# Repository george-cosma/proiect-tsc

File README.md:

# Openbook - Proiect TSC - by Cosma George

## Block Diagram

## Overview ESP32

1. **GND (All 11 pins)** - Connected to the ground plane
2. **3V3 (Pin 2)** - Connected to the 3.3V power rail
3. **EN (Pin 3)** - Enable pin - activates the ESP32-C6 when power is applied.
4. **IO0 (Pin 8)** - INT_RTC (RTC Interrupt) connects to the RTC module to receive time-based interrupts
5. **IO1 (Pin 9)** - 32KHz clock signal received from Oscilator
6. **IO2 (Pin 27)** - MISO (SPI Master In Slave Out). Connects to External Storage, External I/O and E-Paper Display Header
7. **IO3 (Pin 26)** - EPD_BUSY connects to the E-Paper display's busy signal to monitor when the display is busy
8. **IO4 (Pin 4)** - SS_SD (SD Card Chip Select)
9. **IO5 (Pin 5)** - EPD_DC (E-Paper Display Data/Command) to command the E-Paper Display via the Header
10. **IO6 (Pin 6)** - SCK (SPI Clock) to provide a clock frame of reference to communicate via SPI
11. **IO7 (Pin 7)** - MOSI (SPI Master Out Slave In) Connects to External Storage, External I/O and E-Paper Display Header
12. **IO8 (Pin 10)** - GPIO8 general purpose I/O, connected to a test pad (?)
13. **IO9 (Pin 15)** - IO/BOOT connected to an external push button with pull-up resistors.
14. **I10 (Pin 11)** - EPD_CS (E-Paper Display Chip Select) connects directly to the E-Paper Display Header to select when comunicating/receiving data from it.
15. **IO11 (Pin 11)** - FLASH_CS (SPI Flash Chip Select) connects to the NOR Flash memory to select when communicating/receiving data from it.
16. **IO12 (Pin 12)** - USB_D- (USB Data-) connects directly to the USB-C connector and is used for USB communication via UART.
17. **IO13 (Pin 13)** - USB_D+ (USB Data+) connects directly to the USB-C connector and is used for USB communication via UART.
18. **IO15 (Pin 14)** - IO/CHANGE connected to a push button with pull-up resistors, for user input
19. **TXD0/GPIO16 (Pin 25)** - TX (UART Transmit) connected to test pads - for debugging or programming
20. **RXD0/GPIO17 (Pin 24)** - RX (UART Receive) connected to test pads - for debugging or programming
21. **IO18 (Pin 16)** - RTC_RST (RTC Reset) connects to the reset pin of the real-time clock module
22. **IO19 (Pin 17)** - I2C_PW (I2C Power control) controls power to the I2C peripherals
23. **IO20 (Pin 18)** - EPD_3V3_C (E-Paper Display 3.3V control) controls power to the E-Paper display via a transistor. Used to turn on/off the display to save power when not in use.
24. **IO21 (Pin 19)** - SDA (I2C Data) connects to the I2C peripherals for data communication
25. **IO22 (Pin 20)** - SCL (I2C Clock) connects to the I2C peripherals for clock signal
26. **IO23 (Pin 21)** - EPD_RST (E-Paper Display Reset) connects to the E-Paper display's reset pin to reset the display when needed

## Components overview

1. **ESP32-C6-WROOM-1-N8**
   - Purpose: Main microcontroller/SoC
   - Interfaces: Everything
2. **W25Q512JVEIQ**
   - Purpose: External NOR flash memory
   - Interface: SPI
3. **MAX17048G+T10**
   - Purpose: IC to monitor Li-Po battery level
   - Interface: I2C
4. **XC6220A331MR-G**
   - Purpose: LDO voltage regulator
   - Interface: None (power supply)
5. **USBLC6-2SC6Y**
   - Purpose: USB ESD protection IC
   - Interface: USB D+/D- UART lines
6. **MCP73831**
   - Purpose: Single-cell Li-Po battery charging controller
   - Interface: None (power supply)
7. **BME688**
   - Purpose: Environmental sensor
   - Interface: I2C
8. **BD5229G-TR + Buttons**
   - Purpose: Voltage supervisor + Buttons
   - Interface: GPIO
9. **DS3231SN**
   - Purpose: Real-time clock with crystal oscillator
   - Interface: I2C and GPIO
10. **112A-TAAR-R03_ATTEND**
    - Purpose: SD card slot for storage
    - Interface: SPI
11. **FH34SRJ-24S-0.5SH_99_**
    - Purpose: E-Paper Display Headder
    - Interface: SPI + GPIO
12. **SAMACSYS_PARTS_USB4110-GF-A**
    - Purpose: USB-C connector
    - Interface: USB D+/D- UART

## Bill of Materials

| Qty | Device                       | Value                                    | Parts                                                                                                       | Description                                                                                                                   | BUY                                                                                                                                | DATASHEET                                                                                                                             |
|-----|------------------------------|------------------------------------------|-------------------------------------------------------------------------------------------------------------|-------------------------------------------------------------------------------------------------------------------------------|------------------------------------------------------------------------------------------------------------------------------------|---------------------------------------------------------------------------------------------------------------------------------------|
| 1   | 112A-TAAR-R03_ATTEND         | -                                        | J4                                                                                                          | Micro SD Card Socket, Push-Push Type, Top Mount,   SMT, H=1.83mm, 10u                                                         | [Buy here](https://www.tme.eu/ro/details/mcc-sdmicro/conectori-pentru-cartele/attend/112a-taar-r03/)                                           | [Datasheet here](https://cdn.soselectronic.com/productdata/bd/ac/42954337/112a-taar-r03.pdf)                                                            |
| 1   | 744043680IND_4828-WE-TPC_WRE | 68uH                                     | L1                                                                                                          |                                                                                                                               | [Buy here](https://ro.mouser.com/ProductDetail/Wurth-Elektronik/744043008?qs=PGXP4M47uW6hG5GeMvqOSQ%3D%3D)                                     | [Datasheet here](https://www.we-online.com/components/products/datasheet/744043008.pdf)                                                                 |
| 1   | ADAFRUIT_LEDCHIP-LED0603     | -                                        | CHG_LED                                                                                                     | LED                                                                                                                           | [Buy here](https://ro.mouser.com/ProductDetail/ROHM-Semiconductor/CSL1104WBBW1?qs=DRkmTr78QAQ%252BqzFWy9Kqog%3D%3D)                            | [Datasheet here](https://fscdn.rohm.com/en/products/databook/datasheet/opto/led/chip_mono/csl1104wbbw1-e.pdf)                                           |
| 2   | AVX SD0805S020S1R0           | -                                        | D2, D7                                                                                                      | Schottky Barrier Rectifier   Diode                                                                                            | [Buy here](https://ro.mouser.com/ProductDetail/KYOCERA-AVX/SD0805S020S1R0?qs=jCA%252BPfw4LHbpkAoSnwrdjw%3D%3D)                                 | [Datasheet here](https://ro.mouser.com/datasheet/2/40/schottky-3165252.pdf)                                                                             |
| 1   | BD5229G-TR                   | -                                        | IC1                                                                                                         | Voltage Detector with Adjustable Delay Time                                                                                   | [Buy here](https://ro.mouser.com/ProductDetail/ROHM-Semiconductor/BD5229G-TR?qs=4kLU8WoGk0vvnhrrYwdszw%3D%3D)                                  | [Datasheet here](https://fscdn.rohm.com/en/products/databook/datasheet/ic/power/voltage_detector/bd52xxg-e.pdf)                                         |
| 1   | BME688                       | -                                        | SENSOR2                                                                                                     | Integrated Environmental   Unit                                                                                               | [Buy here](https://ro.mouser.com/ProductDetail/Bosch-Sensortec/BME688?qs=IS%252B4QmGtzzqQoVDscqwx3A%3D%3D)                                     | [Datasheet here](https://ro.mouser.com/datasheet/2/783/bst_bme688_fl000-2307034.pdf)                                                                    |
| 1   | Button                       | BOOT_BUTTON, CHANGE_BUTTON_ RESET_BUTTON | U$1, U$2, U$3                                                                                               |                                                                                                                               | [Buy here](https://ro.mouser.com/ProductDetail/Panasonic/EVQ-9P701P?qs=NPkb10g2yLBKCwpELvsGNg%3D%3D)                                           | [Datasheet here](https://4donline.ihs.com/images/VipMasterIC/IC/PANA/PANAS45028/PANAS45028-1.pdf?hkey=CECEF36DEECDED6468708AAF2E19C0C6)                 |
| 1   | Capacitor                    | 0.1uF/50V                                | EPD_C5                                                                                                      | CAPACITOR, European symbol                                                                                                    | [Buy here](https://ro.mouser.com/ProductDetail/WIMA/SMDIC03100KA00MP00?qs=sGAEpiMZZMukHu%252BjC5l7YTpCIjlvjqqOhx6cMTURzRs%3D)                  | [Datasheet here](https://ro.mouser.com/datasheet/2/440/e_WIMA_SMD_PPS-1139945.pdf)                                                                      |
| 8   | Capacitor                    | 100nF                                    | C1, C2, C4_USB, C6, C8, C9, C10, C_DELAY                                                                    | CAPACITOR, European symbol                                                                                                    | [Buy here](https://ro.mouser.com/ProductDetail/Vishay-Vitramon/VJ1210Y104KBBAT4X?qs=sGAEpiMZZMukHu%252BjC5l7YUsqw7r0AP18aXzCLTFnl8Y%3D)        | [Datasheet here](https://www.vishay.com/doc?45198)                                                                                                      |
| 1   | Capacitor                    | 10uF                                     | C7                                                                                                          | CAPACITOR, European symbol                                                                                                    | [Buy here](https://ro.mouser.com/ProductDetail/KYOCERA-AVX/KGM03DS60E106MH?qs=sGAEpiMZZMukHu%252BjC5l7YWACoop%252BoD4TOu1wAFQEK4E%3D)          | [Datasheet here](https://ro.mouser.com/datasheet/2/40/cx5r_KGM-3223198.pdf)                                                                             |
| 1   | Capacitor                    | 1uF                                      | C5                                                                                                          | CAPACITOR, European symbol                                                                                                    | [Buy here](https://ro.mouser.com/ProductDetail/WIMA/SMDTC04100VA00KR00?qs=sGAEpiMZZMukHu%252BjC5l7YeyzaTQ4jBxXydaOoMKRkJQ%3D)                  | [Datasheet here](https://ro.mouser.com/datasheet/2/440/e_WIMA_SMD_PET-1139826.pdf)                                                                      |
| 9   | Capacitor                    | 1uF/50V                                  | EPD_C1, EPD_C2, EPD_C6,   EPD_C7, EPD_C8, EPD_C9, EPD_C10, EPD_C11, EPD_C12                                 | CAPACITOR, European symbol                                                                                                    | [Buy here](https://ro.mouser.com/ProductDetail/WIMA/SMDTC04100VA00KR00?qs=sGAEpiMZZMukHu%252BjC5l7YeyzaTQ4jBxXydaOoMKRkJQ%3D)                  | [Datasheet here](https://ro.mouser.com/datasheet/2/440/e_WIMA_SMD_PET-1139826.pdf)                                                                      |
| 5   | Capacitor                    | 4.7uF                                    | C1_BAT, C1_BAT1, C1_BAT2, C2_BAT, C5_USB                                                                    | CAPACITOR, European symbol                                                                                                    | [Buy here](https://ro.mouser.com/ProductDetail/WIMA/SMDTD04470YA00KS00?qs=sGAEpiMZZMukHu%252BjC5l7YTpCIjlvjqqOpdXtMIjonJE%3D)                  | [Datasheet here](https://ro.mouser.com/datasheet/2/440/e_WIMA_SMD_PET-1139826.pdf)                                                                      |
| 1   | Capacitor                    | 4.7uF/25V                                | C4                                                                                                          | CAPACITOR, European symbol                                                                                                    | [Buy here](https://ro.mouser.com/ProductDetail/WIMA/SMDTD04470YA00KS00?qs=sGAEpiMZZMukHu%252BjC5l7YTpCIjlvjqqOpdXtMIjonJE%3D)                  | [Datasheet here](https://ro.mouser.com/datasheet/2/440/e_WIMA_SMD_PET-1139826.pdf)                                                                      |
| 1   | CPH3225A                     | -                                        | C10_SUPERCAP                                                                                                | Cap 0.011F 3.3V 1210 Flat Check availability                                                                                  | [Buy here](https://ro.mouser.com/ProductDetail/Seiko-Semiconductors/CPH3225A?qs=3etwrb1wR%252BhUOph6lAO7eg%3D%3D)                              | [Datasheet here](https://ro.mouser.com/datasheet/2/360/Seiko_Instruments_MicroBattery_E_20230330_2024Jan_-3561061.pdf)                                  |
| 2   | DMG2305UX-7                  | 20V/4.2A/52mO/1.4W                       | Q1, Q2                                                                                                      | P-channel MOSFETs                                                                                                             | [Buy here](https://ro.mouser.com/ProductDetail/Diodes-Incorporated/DMG2305UX-7?qs=L1DZKBg7t5F%2FNBHrjfxC%252Bg%3D%3D)                          | [Datasheet here](https://www.diodes.com/assets/Datasheets/DMG2305UX.pdf)                                                                                |
| 1   | DS3231SN#                    | -                                        | U3                                                                                                          | Real Time Clock Serial 16-Pin SOIC W T/R     Check availability                                                               | [Buy here](https://ro.mouser.com/ProductDetail/Analog-Devices-Maxim-Integrated/DS3231SN?qs=1eQvB6Dk1vhUlr8%2FOrV0Fw%3D%3D)                     | [Datasheet here](https://ro.mouser.com/datasheet/2/609/DS3231-3421123.pdf)                                                                              |
| 1   | ESP32-C6-WROOM-1-N8          | -                                        | U2                                                                                                          |                                                                                                                               | [Buy here](https://ro.mouser.com/ProductDetail/Espressif-Systems/ESP32-C6-WROOM-1-N8?qs=8Wlm6%252BaMh8ST02Gmwp74cw%3D%3D)                      | [Datasheet here](https://ro.mouser.com/datasheet/2/891/Espressif_ESP32_C6_WROOM_1__Datasheet_V0_1_PRELIMI-3239987.pdf)                                  |
| 1   | FH34SRJ-24S-0.5SH_99_        | -                                        | J1                                                                                                          |  (0.50mm)   Surface Mount, Right Angle                                                                                        | [Buy here](https://ro.mouser.com/ProductDetail/Hirose-Connector/FH34SRJ-24S-0.5SH99?qs=vcbW%252B4%252BSTIpKBl5ap9J8Fw%3D%3D)                   | [Datasheet here](https://ro.mouser.com/datasheet/2/185/FH34SRJ_24S_0_5SH_99__CL0580_1255_6_99_2DDrawing_0-1615044.pdf)                                  |
| 1   | MAX17048G+T10                | -                                        | U4                                                                                                          |                                                                                                                               | [Buy here](https://ro.mouser.com/ProductDetail/Analog-Devices-Maxim-Integrated/MAX17048G%2bT10?qs=D7PJwyCwLAoGnnn8jEPRBQ%3D%3D)                | [Datasheet here](https://ro.mouser.com/datasheet/2/609/MAX17048_MAX17049-3469099.pdf)                                                                   |
| 3   | MBR0530                      | -                                        | D3, D4, D5                                                                                                  | ON SEMICONDUCTOR - MBR0530 - DIODE, SCHOTTKY, 0.5A,   30V, SOD-123                                                            | [Buy here](https://ro.mouser.com/ProductDetail/onsemi/MBR0530T3G?qs=3JMERSakebpEmdUS6GetdQ%3D%3D)                                              | [Datasheet here](https://www.onsemi.com/PowerSolutions/product.do?id=MBR0530T3G)                                                                        |
| 1   | MCP73831                     | -                                        | U10                                                                                                         | MCP73831T Li-Ion, Li-Pol   Controller                                                                                         | [Buy here](https://ro.mouser.com/ProductDetail/Microchip-Technology/MCP73831T-2ACI-OT?qs=yUQqVecv4qvbBQBGbHx0Mw%3D%3D)                         | [Datasheet here](https://ro.mouser.com/datasheet/2/268/MCP73831_Family_Data_Sheet_DS20001984H-3441711.pdf)                                              |
| 6   | PGB1010603MR                 | -                                        | D6, D8, D9, D10, D11, D12                                                                                   |                                                                                                                               | [Buy here](https://ro.mouser.com/ProductDetail/Littelfuse/PGB1010603MR?qs=gu7KAQ731URLg4GSnNNN7Q%3D%3D)                                        | [Datasheet here](https://www.littelfuse.com/assetdocs/pulseguard-esd-suppressors-pgb1-datasheet?assetguid=8a337998-d54d-466b-be4e-dc5bcd1f9321)         |
| 1   | QWIIC_CONNECTORJS-1MM        | -                                        | J3                                                                                                          | SparkFun I2C Standard   Qwiic Connector                                                                                       | [Buy here](https://www.sparkfun.com/qwiic-jst-connector-smd-4-pin-horizontal.html)                                                             | [Datasheet here](https://cdn.sparkfun.com/assets/parts/1/2/2/8/9/Qwiic_Connector_Datasheet.pdf)                                                         |
| 1   | RCL_CPOL-EUCT3528            | 100uF TANT                               | C3                                                                                                          | POLARIZED CAPACITOR, European symbol                                                                                          | [Buy here](https://ro.mouser.com/ProductDetail/Vishay-Sprague/593D107X9020E2TE3?qs=sGAEpiMZZMsh%252B1woXyUXj7FzGMN%252BX%252BZrA47dYxLY0LY%3D) | [Datasheet here](https://www.vishay.com/doc?40005)                                                                                                      |
| 1   | Resistance                   | 0.47                                     | R3                                                                                                          | RESISTOR, European symbol                                                                                                     | [Buy here](https://ro.mouser.com/ProductDetail/Panasonic/ERJ-14BQFR47U?qs=sGAEpiMZZMukHu%252BjC5l7Ye4WQ9FrfA3YXh5QopT%252BLe8%3D)              | [Datasheet here](https://industrial.panasonic.com/cdbs/www-data/pdf/RDN0000/AOA0000C313.pdf)                                                            |
| 1   | Resistance                   | 100K                                     | R1_PWRBUS                                                                                                   | RESISTOR, European symbol                                                                                                     | [Buy here](https://ro.mouser.com/ProductDetail/Vishay-Thin-Film/PTN0603E1003BBT1?qs=sGAEpiMZZMukHu%252BjC5l7YTJuwIl8JpxyJ2Y%2FdokIqGc%3D)      | [Datasheet here](https://www.vishay.com/doc?60026)                                                                                                      |
| 16  | Resistance                   | 10K                                      | R1, R1_PINH, R1_PINH1,   R2_PINH, R2_PINH1, R4, R5, R6, R7, R8, R9, R10, R_BOOT, R_CHANGE, R_CL1,   R_RESET | RESISTOR, European symbol                                                                                                     | [Buy here](https://ro.mouser.com/ProductDetail/Vishay-Draloric/RCA040210K0JNED?qs=sGAEpiMZZMukHu%252BjC5l7YQO3gf4mVmUu96cUBYHYfeM%3D)          | [Datasheet here](https://www.vishay.com/doc?20037)                                                                                                      |
| 1   | Resistance                   | 15                                       | R_CAPACITOR                                                                                                 | RESISTOR, European symbol                                                                                                     | [Buy here](https://ro.mouser.com/ProductDetail/ROHM-Semiconductor/KTR03EZPJ150?qs=sGAEpiMZZMtlubZbdhIBICz%2FtfrlArmddJ1cOrAnKnc%3D)            | [Datasheet here](https://www.rohm.com/datasheet?p=KTR03EZPJ&dist=Mouser&media=referral&source=mouser.com&campaign=Mouser)                               |
| 1   | Resistance                   | 2.2                                      | R2                                                                                                          | RESISTOR, European symbol                                                                                                     | [Buy here](https://ro.mouser.com/ProductDetail/ROHM-Semiconductor/KTR18EZPJ2R2?qs=sGAEpiMZZMtlubZbdhIBICz%2FtfrlArmdtqB%2FNN1ZHWQ%3D)          | [Datasheet here](https://www.rohm.com/datasheet?p=KTR18EZPJ&dist=Mouser&media=referral&source=mouser.com&campaign=Mouser)                               |
| 1   | Resistance                   | 200                                      | R1_BAT                                                                                                      | RESISTOR, European symbol                                                                                                     | [Buy here](https://ro.mouser.com/ProductDetail/ROHM-Semiconductor/KTR10EZPJ201?qs=sGAEpiMZZMtlubZbdhIBIGrVcSH3vih40FduZYz%252BzpI%3D)          | [Datasheet here](https://www.rohm.com/datasheet?p=KTR10EZPJ&dist=Mouser&media=referral&source=mouser.com&campaign=Mouser)                               |
| 1   | Resistance                   | 2K                                       | R2_BAT                                                                                                      | RESISTOR, European symbol                                                                                                     | [Buy here](https://ro.mouser.com/ProductDetail/Vishay-Sfernice/P0805Y2001BBW?qs=sGAEpiMZZMtlubZbdhIBIL5MhBxehHgV0bOCcoqDPYA%3D)                | [Datasheet here](https://4donline.ihs.com/images/VipMasterIC/IC/VISH/VISH-S-A0007087424/VISH-S-A0007087424-1.pdf?hkey=CECEF36DEECDED6468708AAF2E19C0C6) |
| 2   | Resistance                   | 5K1                                      | R2-USB, R2-USB1                                                                                             | RESISTOR, European symbol                                                                                                     | [Buy here](https://ro.mouser.com/ProductDetail/Vishay-Dale/TNPW04025K10BYEP?qs=sGAEpiMZZMtlubZbdhIBIJ2VesJ5mRFWaQfYu47si8Y%3D)                 | [Datasheet here](https://www.vishay.com/doc?28758)                                                                                                      |
| 1   | SAMACSYS_PARTS_USB4110-GF-A  | -                                        | J2                                                                                                          | CONN USB 2.0 TYPE-C R/A   SMT                                                                                                 | [Buy here](https://ro.mouser.com/ProductDetail/GCT/USB4110-GF-A?qs=KUoIvG%2F9IlYiZvIXQjyJeA%3D%3D)                                             | [Datasheet here](https://ro.mouser.com/datasheet/2/837/GCT_USB4110_Product_Drawing___20k_cycles-3455479.pdf)                                            |
| 1   | SI1308EDL-T1-GE3             | -                                        | Q3                                                                                                          | MOSFET N-Ch 30V 1.5A TrenchFET SC70 Vishay   Si1308EDL-T1-GE3 N-channel MOSFET Transistor, 1.5 A, 30 V, 3-Pin SC-70           | [Buy here](https://ro.mouser.com/ProductDetail/Vishay-Semiconductors/SI1308EDL-T1-GE3?qs=bX1%252BNvsK%2FBramh9tgpOaEw%3D%3D)                   | [Datasheet here](https://www.vishay.com/doc?63399)                                                                                                      |
| 1   | USBLC6-2SC6Y                 | -                                        | D1                                                                                                          | Low Cap. ESD Protection   Auto SOT-23-6 STMicroelectronics USBLC6-2SC6Y, Dual Uni-Directional TVS Diode   Array, 6-Pin SOT-23 | [Buy here](https://ro.mouser.com/ProductDetail/STMicroelectronics/USBLC6-2SC6Y?qs=gNDSiZmRJS%2FOgDexvXkdow%3D%3D)                              | [Datasheet here](https://ro.mouser.com/datasheet/2/389/usblc6_2sc6y-1852505.pdf)                                                                        |
| 1   | VARISTOR CN1812              | -                                        | PFMF.050.1                                                                                                  | VARISTOR                                                                                                                      | [Buy here](https://ro.mouser.com/ProductDetail/Schurter/PFMF.050.2?qs=1auRipcfynCums5v1iucSA%3D%3D)                                            | [Datasheet here](https://ro.mouser.com/datasheet/2/358/typ_PFMF-1275918.pdf)                                                                            |
| 1   | W25Q512JVEIQ                 | -                                        | U1                                                                                                          |                                                                                                                               | [Buy here](https://ro.mouser.com/ProductDetail/Winbond/W25Q512JVEIQ?qs=l7cgNqFNU1jw6svr3at6tA%3D%3D)                                           | [Datasheet here](https://ro.mouser.com/datasheet/2/949/Winbond_W25Q512JV_Datasheet-3240039.pdf)                                                         |
| 1   | XC6220A331MR-G               | -                                        | IC4                                                                                                         | LDO Voltage Regulators                                                                                                        | [Buy here](https://ro.mouser.com/ProductDetail/Torex-Semiconductor/XC6220A331MR-G?qs=AsjdqWjXhJ8ZSWznL1J0gg%3D%3D)                             | [Datasheet here](https://ro.mouser.com/datasheet/2/760/xc6220-3371556.pdf)                                                                              |
| 1   | Battery                      | -                                        | -                                                                                                           | CELLEVIA BATTERIES LP584174, 3.7V 1800 mAh | [Buy here](https://www.tme.eu/ro/details/accu-lp584174_cl/acumulatori/cellevia-batteries/l584174/) | [Datasheet here](https://www.tme.eu/Document/e0683d8c34e6d878124489f71bffb6ee/cel0014.pdf) |
| 1   | E-Paper Display              | -                                        | -                                                                                                           | 7.5''  800x480 px 125 DPI | [Buy here](https://www.waveshare.com/7.5inch-e-paper-hat.htm) | [Datasheet here](https://files.waveshare.com/upload/6/60/7.5inch_e-Paper_V2_Specification.pdf) |

## Implementation Notes/Details

- I've attempted to replicate the schematic as closely as possible, but there might be minor differences in terms of label size, label and text positioning,
compactness of components.
- The PCB was routed 100% manually, with no auto-router used. Both a top and bottom ground plane were used, as per the design requirements, and extensive via stitching was used to ensure a low-impedance ground connection. Via stiching can be removed if design parameters change, as additional vias for ground connectivity have been added to the design outside of the stiching process.
- Two visas were used for I2C_PW line, as it was unavoidable to route without crossing another power line. All power lines were routed using 0.3mm without vias and kept as short as possible, and all signal lines were routed using 0.2mm using vias.  
- PCB Thickness was modified to 1mm to ensure it, alongside the display, were able to fit within the given enclosure.
- PCB holes were added for the battery, ESP antenna, and the display header to allow for the ribbon cable to be inserted.
- Silkscreen was made with minimality in mind. Additional marks (lines, extra text) were added when needed to ensure readability.
- Accepted clearence error for USB-C connector.

## Other Images

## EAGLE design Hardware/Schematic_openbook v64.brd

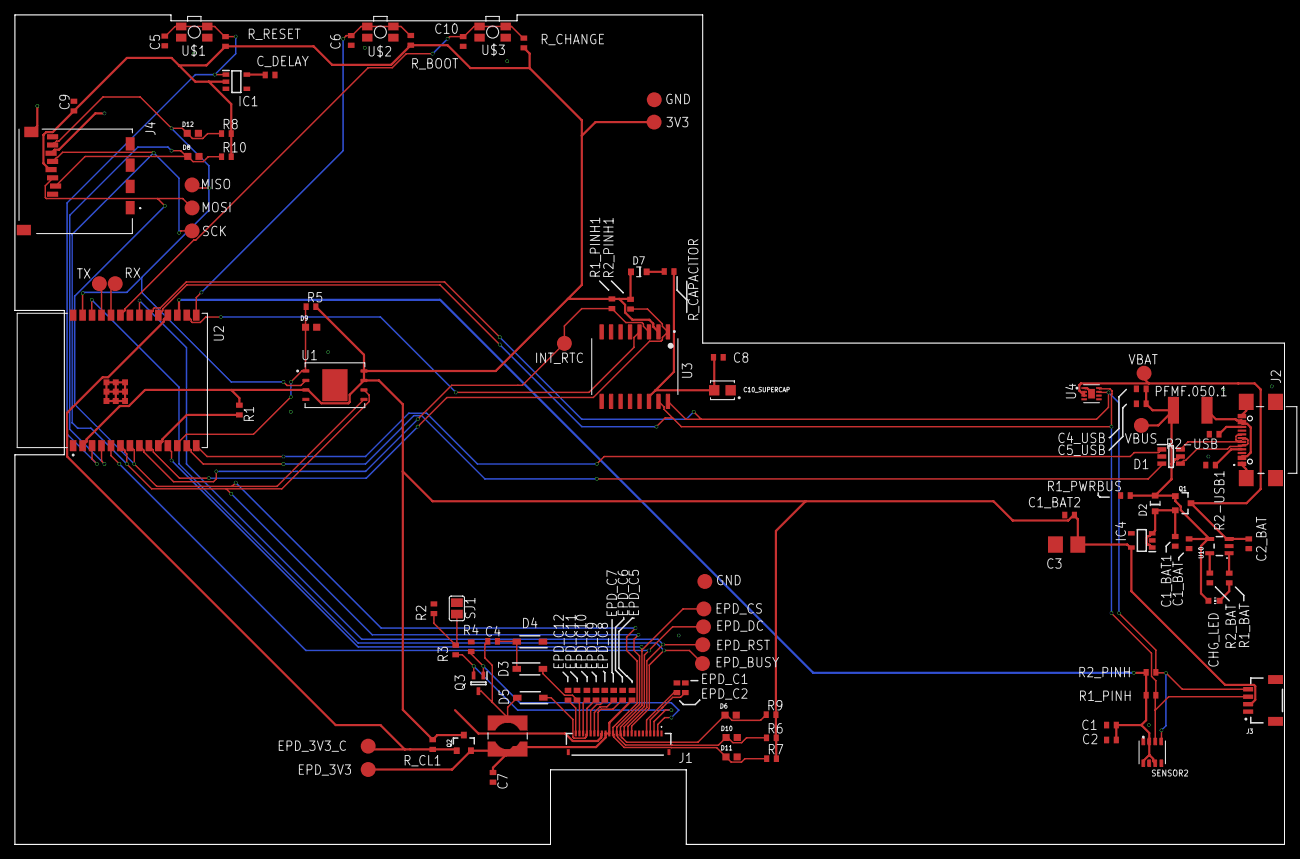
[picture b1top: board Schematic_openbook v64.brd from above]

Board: 2 copper layers, 170.2 x 111.2 mm, 103 parts (0 on the bottom side), 55 nets.

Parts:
C1, C2, C4_USB, C6, C8, C9, C10: 100nF; EAGLE-LTSPICE_C0402
C1_BAT, C1_BAT1, C1_BAT2, C2_BAT, C5_USB: 4.7uF; EAGLE-LTSPICE_C0402
C3: 100uF TANT; RCL_CT3528
C4: 4.7uF/25V; EAGLE-LTSPICE_C0402
C5: 1uF; EAGLE-LTSPICE_C0402
C7: 10uF; EAGLE-LTSPICE_C0402
C10_SUPERCAP: CPH3225A; CAPCP3225X100N
CHG_LED: NA; ADAFRUIT_CHIP-LED0603
C_DELAY: 100nF; EAGLE-LTSPICE_C0402
D1: USBLC6-2SC6Y; SOT95P280X145-6N
D2: ESP32_WROVER_AVX---SD0805S020S1R0_AVX_SD0805S020S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; ESP32_WROVER_AVX---SD0805S020S1R0_AVX_SD0805S020S1R0_0
D3, D4, D5: MBR0530; SOD3716X135N
D6, D8, D9, D10, D11, D12: PGB1010603MR; DIOC1608X36N
D7: SD0805S020S1R0; ESP32_WROVER_AVX---SD0805S020S1R0_AVX_SD0805S020S1R0_0
EPD_C1, EPD_C2, EPD_C6, EPD_C7, EPD_C8, EPD_C9, EPD_C10, EPD_C11, EPD_C12: 1uF/50V; EAGLE-LTSPICE_C0402
EPD_C5: 0.1uF/50V; EAGLE-LTSPICE_C0402
IC1: BD5229G-TR; SOT95P280X125-5N
IC4: XC6220A331MR-G; SOT95P280X120-5N
J1: FH34SRJ-24S-0.5SH_99_; FH34SRJ24S05SH99
J2: SAMACSYS_PARTS_USB4110-GF-A; SAMACSYS_PARTS_USB4110GFA
J3: QWIIC_RIGHT_ANGLE; JST04_1MM_RA
J4: 112A-TAAR-R03_ATTEND; 112ATAARR03ATTEND
L1: 68uH; IND_4828-WE-TPC_WRE
PFMF.050.1: ESP32C6_VARISTORCN1812; ESP32C6_VARISTOR_CT/CN1812
Q1, Q2: 20V/4.2A/52mΩ/1.4W; ESP32_WROVER_SPARKFUN-DISCRETESEMI_SOT23-3
Q3: SI1308EDL-T1-GE3; SOT65P210X110-3N
R1, R1_PINH, R1_PINH1, R2_PINH, R2_PINH1, R5, R6, R7, R8, R9, R10: 10K; ESP32_WROVER_EAGLE-LTSPICE_R0402
R1_BAT: 200; ESP32_WROVER_EAGLE-LTSPICE_R0402
R1_PWRBUS: 100K; ESP32_WROVER_EAGLE-LTSPICE_R0402
R2: 2.2; ESP32_WROVER_EAGLE-LTSPICE_R0402
R2-USB, R2-USB1: 5K1; ESP32_WROVER_EAGLE-LTSPICE_R0402
R2_BAT: 2K; ESP32_WROVER_EAGLE-LTSPICE_R0402
R3: 0.47; ESP32_WROVER_EAGLE-LTSPICE_R0402
R4: 10k; ESP32_WROVER_EAGLE-LTSPICE_R0402
R_BOOT: 10K; ESP32_WROVER_EAGLE-LTSPICE_R0402
R_CAPACITOR: 15; ESP32_WROVER_EAGLE-LTSPICE_R0402
R_CHANGE: 10K; ESP32_WROVER_EAGLE-LTSPICE_R0402
R_CL1: 10K; ESP32_WROVER_EAGLE-LTSPICE_R0402
R_RESET: 10K; ESP32_WROVER_EAGLE-LTSPICE_R0402
SENSOR2: BME688; ESP32_WROVER_BME680_PSON80P300X300X100-8N
SJ1: NA; SJ
TP1, TP2, TP3, TP4, TP5, TP6, TP7, TP8, TP9, TP10, TP11, TP12, TP13, TP14, TP15, TP16, TP17: TPTP20R; TP20R
U1: W25Q512JVEIQ; SON127P600X800X80-9N
U2: ESP32-C6-WROOM-1-N8; XCVR_ESP32-C6-WROOM-1-N8
U3: DS3231SN#; SOIC127P1032X265-16N
U4: MAX17048G+T10; SON50P200X200X80-9N
U10: MCP73831; ESP32_WROVER_SPARKFUN-IC-POWER_SOT23-5
U$1: RESET_BUTTON; MYBUTTON
U$2: BOOT_BUTTON; MYBUTTON
U$3: CHANGE_BUTTON; MYBUTTON

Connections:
3V3: C1_BAT2.1, C3.+, C9.1, D7.2, IC1.2, IC4.5, J3.2, J4.P4, Q2.3, R1.1, R1_PINH1.2, R2_PINH1.2, R5.2, R6.2, R7.2, R8.2, R9.2, R10.2, R_BOOT.1, R_CHANGE.1, R_CL1.1, R_RESET.1, TP16.TP, U1.3, U1.7, U1.8, U2.2, U3.2
32KHZ: R2_PINH1.1, U2.9, U3.1
DN: D1.4, J2.A7, J2.B7
DP: D1.6, J2.A6, J2.B6
EPD_3V3: C7.1, EPD_C5.1, J1.15, J1.16, L1.2, Q2.2, TP17.TP
EPD_3V3_C: Q2.1, R_CL1.2, TP13.TP, U2.18
EPD_BUSY: J1.9, TP9.TP, U2.26
EPD_CS: D6.1, J1.12, R9.1, TP10.TP, U2.11
EPD_DC: J1.11, TP11.TP, U2.5
EPD_RST: J1.10, TP12.TP, U2.21
FLASH_CS: D9.1, R5.1, U1.1, U2.12
GDR: J1.2, Q3.1, R4.2
GND: C1.2, C1_BAT.2, C1_BAT1.2, C1_BAT2.2, C2.2, C2_BAT.2, C3.-, C4_USB.2, C5.2, C5_USB.2, C6.2, C7.2, C8.2, C9.2, C10.2, C10_SUPERCAP.1, C_DELAY.2, D1.2, D4.1, D6.2, D8.2, D9.2, D10.2, D11.2, D12.2, EPD_C1.2, EPD_C2.2, EPD_C5.2, EPD_C6.2, EPD_C7.2, EPD_C8.2, EPD_C9.2, EPD_C10.2, EPD_C11.2, EPD_C12.2, IC1.3, IC4.2, J1.8, J1.17, J1.MP1, J1.MP2, J2.A1, J2.A12, J2.B1, J2.B12, J2.MP1, J2.MP2, J2.MP3, J2.MP4, J3.1, J4.G1, J4.G2, J4.G3, J4.G4, J4.P6, R1_PWRBUS.1, R2.1, R2-USB.2, R2-USB1.1, R2_BAT.1, R4.1, SENSOR2.1, SENSOR2.5, SENSOR2.7, SJ1.1, TP4.TP, TP5.TP, U1.4, U1.9, U2.1, U2.28, U2.29_1, U2.29_2, U2.29_3, U2.29_4, U2.29_5, U2.29_6, U2.29_7, U2.29_8, U2.29_9, U3.13, U4.1, U4.4, U4.6, U4.9, U10.2, U$1.1, U$1.2, U$2.1, U$2.2, U$3.1, U$3.2
GPIO8: R1.2, U2.10
I2C_PW: C1.1, C2.1, R1_PINH.2, R2_PINH.2, SENSOR2.2, SENSOR2.6, SENSOR2.8, U2.17
INT_RTC: R1_PINH1.1, TP15.TP, U2.8, U3.3
IO/BOOT: C6.1, R_BOOT.2, U2.15, U$2.3, U$2.4
IO/CHANGE: C10.1, R_CHANGE.2, U2.23, U$3.3, U$3.4
MISO: D12.1, J4.P7, R8.1, TP6.TP, U1.2, U2.27
MOSI: D11.1, J1.14, J4.P3, R7.1, TP7.TP, U1.5, U2.7
unnamed: C1_BAT1.1, D2.1, IC4.1, IC4.3, Q1.2
unnamed: J2.B5, R2-USB.1
unnamed: CHG_LED.C, R1_BAT.1
unnamed: R1_BAT.2, U10.1
unnamed: EPD_C1.1, J1.4
unnamed: J2.A5, R2-USB1.2
unnamed: C4.1, D3.1, D4.2
unnamed: R2_BAT.2, U10.5
unnamed: EPD_C2.1, J1.5
unnamed: EPD_C6.1, J1.18
unnamed: EPD_C7.1, J1.19
unnamed: EPD_C8.1, J1.20
unnamed: C_DELAY.1, IC1.5
unnamed: EPD_C10.1, J1.22
unnamed: D7.1, R_CAPACITOR.1
unnamed: EPD_C12.1, J1.24
PREVGH: D5.1, EPD_C9.1, J1.21
PREVGL: D3.2, EPD_C11.1, J1.23
RESE: J1.3, Q3.2, R3.2
RESE': R2.2, R3.1, SJ1.2
RESET: C5.1, IC1.1, R_RESET.2, U2.3, U$1.3, U$1.4
RTC_RST: U2.16, U3.4
RX: TP2.TP, U2.24
SCK: D10.1, J1.13, J4.P5, R6.1, TP8.TP, U1.6, U2.6
SCL: J3.4, R2_PINH.1, SENSOR2.4, U2.20, U3.16, U4.7
SDA: J3.3, R1_PINH.1, SENSOR2.3, U2.19, U3.15, U4.8
SRC: C4.2, D5.2, L1.1, Q3.3
SS_SD: D8.1, J4.P2, R10.1, U2.4
TX: TP1.TP, U2.25
USB_D+: D1.1, U2.14
USB_D-: D1.3, U2.13
VBAT: C2_BAT.1, Q1.3, TP3.TP, U4.2, U4.3, U10.3
VBUS: C1_BAT.1, C4_USB.1, C5_USB.1, CHG_LED.A, D1.5, D2.2, PFMF.050.1.2, Q1.1, R1_PWRBUS.2, TP14.TP, U10.4
VRTC: C8.1, C10_SUPERCAP.2, R_CAPACITOR.2, U3.14
VUSB: J2.A4, J2.A9, J2.B4, J2.B9, PFMF.050.1.1

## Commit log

2025-04-06 Initial commit (EVD Done)
2025-04-13 Fixed (Review #1)
2025-04-16 Missing via stiching to a component

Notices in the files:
parts and their libraries:
COPYRIGHT: Copyright (C) 2024 Ultra Librarian. All rights reserved.
